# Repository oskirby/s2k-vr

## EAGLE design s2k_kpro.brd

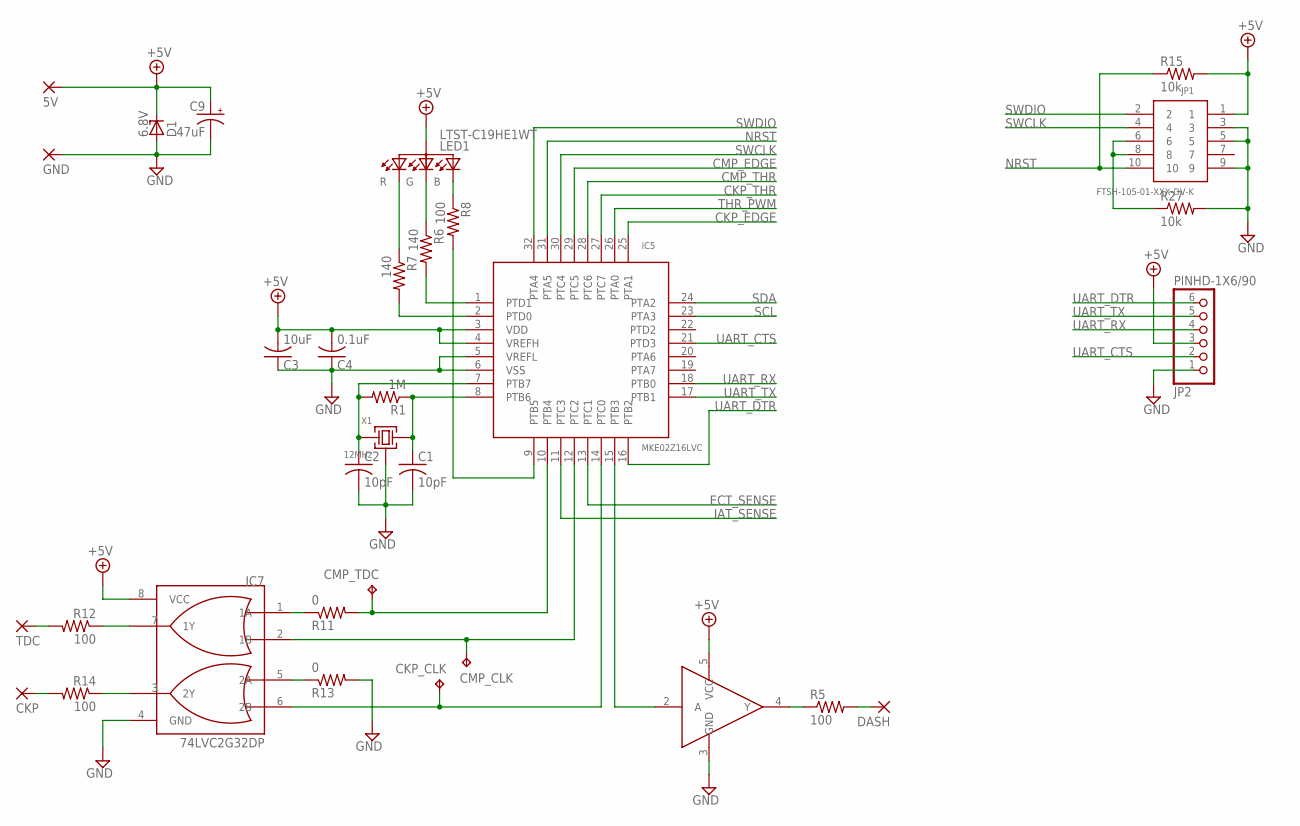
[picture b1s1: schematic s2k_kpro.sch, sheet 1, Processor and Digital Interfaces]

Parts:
5V: 5V; P1-20
C1, C2: 10pF; C0603
C3: 10uF; C0805
C4: 0.1uF; C0603
C9: 47uF; D/7343-31R
CKP: SIGPAD-P1-20; P1-20
CKP_CLK: TPB2,54; B2,54
CMP_CLK: TPB2,54; B2,54
CMP_TDC: TPB2,54; B2,54
D1: 6.8V; SOT23
DASH: SIGPAD-P1-20; P1-20
GND: SIGPAD-P1-20; P1-20
IC5: MKE02Z16LVC; LQFP32-7X7
IC6: 74LVC1G17SE; SOT353
IC7: 74LVC2G32DP; TSSOP8
JP1: FTSH-105-01-XXX-DV-K
JP2: PINHD-1X6/90; 1X06/90
LED1: LTST-C19HE1WT; LED-0606
R1: 1M; R0603
R5, R8, R12, R14: 100; R0603
R6, R7: 140; R0603
R11, R13: 0; R0603
R15, R27: 10k; R0603
TDC: SIGPAD-P1-20; P1-20
X1: 12MHz; SMD4-2520

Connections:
+5V: 5V.TP, C3.2, C4.2, C9.+, D1.3 (C), IC5.3 (VDD), IC5.4 (VREFH), IC6.5 (VCC), IC7.8 (VCC), JP1.1, JP2.3, LED1.4 (ANODE), R15.2; also elsewhere on the board
CAM_CLK: CMP_CLK.TP, IC5.12 (PTC2), IC7.2 (1B)
CAM_OUT: R12.2, TDC.TP
CAM_TDC: CMP_TDC.TP, IC5.10 (PTB4), R11.2
CKP_CLK: CKP_CLK.TP, IC5.14 (PTC0), IC7.6 (2B)
CKP_EDGE: IC5.25 (PTA1); also elsewhere on the board
CKP_THR: IC5.27 (PTC7); also elsewhere on the board
CMP_EDGE: IC5.29 (PTC5); also elsewhere on the board
CMP_THR: IC5.28 (PTC6); also elsewhere on the board
CRANK_OUT: CKP.TP, R14.2
ECT_OUT: DASH.TP, R5.2
ECT_PWM: IC5.15 (PTB3), IC6.2 (A)
ECT_SENSE: IC5.13 (PTC1); also elsewhere on the board
EXTAL: C2.1, IC5.7 (PTB7), R1.2, X1.3 (2)
GND: C1.2, C2.2, C3.1, C4.1, C9.-, D1.1 (A), GND.TP, IC5.5 (VREFL), IC5.6 (VSS), IC6.3 (GND), IC7.4 (GND), JP1.3, JP1.5, JP1.9, JP2.1, R13.2, R27.2, X1.2 (GND), X1.4 (GND); also elsewhere on the board
IAT_SENSE: IC5.11 (PTC3); also elsewhere on the board
LED_B: IC5.9 (PTB5), R8.2
LED_G: IC5.2 (PTD0), R7.2
LED_R: IC5.1 (PTD1), R6.2
unnamed: IC7.7 (1Y), R12.1
unnamed: IC7.1 (1A), R11.1
unnamed: LED1.2 (G), R6.1
unnamed: IC7.5 (2A), R13.1
unnamed: LED1.1 (R), R7.1
unnamed: LED1.3 (B), R8.1
unnamed: IC7.3 (2Y), R14.1
unnamed: IC6.4 (Y), R5.1
unnamed: JP1.6, JP1.8, R27.1
NRST: IC5.31 (PTA5), JP1.10, R15.1; also elsewhere on the board
SCL: IC5.23 (PTA3); also elsewhere on the board
SDA: IC5.24 (PTA2); also elsewhere on the board
SWCLK: IC5.30 (PTC4), JP1.4
SWDIO: IC5.32 (PTA4), JP1.2
THR_PWM: IC5.26 (PTA0); also elsewhere on the board
UART_CTS: IC5.21 (PTD3), JP2.2
UART_DTR: IC5.16 (PTB2), JP2.6
UART_RX: IC5.18 (PTB0), JP2.4
UART_TX: IC5.17 (PTB1), JP2.5
XTAL: C1.1, IC5.8 (PTB6), R1.1, X1.1

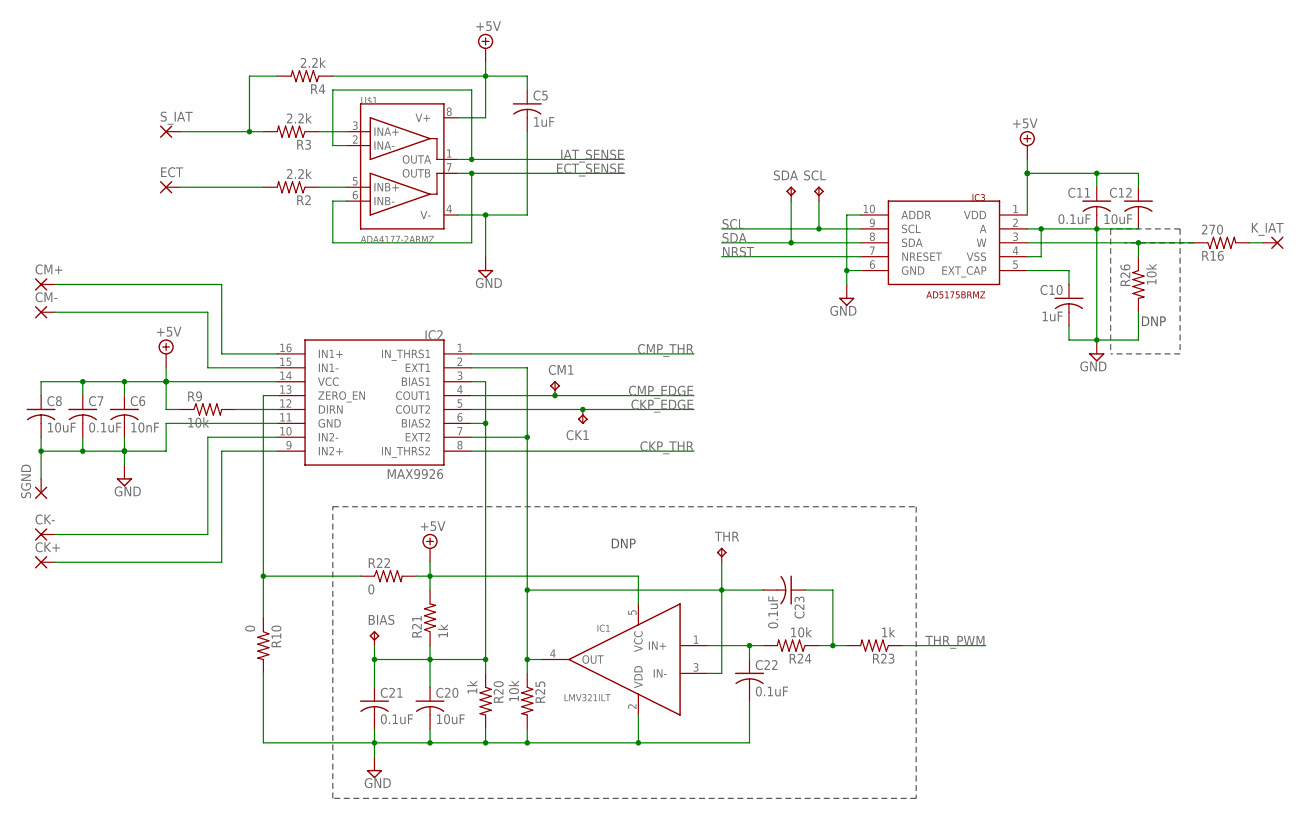
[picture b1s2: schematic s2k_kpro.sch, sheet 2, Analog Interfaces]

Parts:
BIAS: TPB2,54; B2,54
C5, C10: 1uF; C0603
C6: 10nF; C0306
C7, C11, C21, C22, C23: 0.1uF; C0603
C8, C12: 10uF; C0805
C20: 10uF; C0603
CK1: TPB2,54; B2,54
CK+: SIGPAD-P1-20; P1-20
CK-: SIGPAD-P1-20; P1-20
CM1: TPB2,54; B2,54
CM+: SIGPAD-P1-20; P1-20
CM-: SIGPAD-P1-20; P1-20
ECT: SIGPAD-P1-20; P1-20
IC1: LMV321ILT; SOT23-5L
IC2: MAX9926; 16-QSOP
IC3: AD5175BRMZ; MSOP10
K_IAT: SIGPAD-P1-20; P1-20
R2, R3, R4: 2.2k; R0603
R9, R24, R25, R26: 10k; R0603
R10, R22: 0; R0603
R16: 270; R0603
R20, R21, R23: 1k; R0603
SCL: TPB2,54; B2,54
SDA: TPB2,54; B2,54
SGND: SIGPAD-P1-20; P1-20
S_IAT: SIGPAD-P1-20; P1-20
THR: TPB2,54; B2,54
U$1: ADA4177-2ARMZ; MSOP08

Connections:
+5V: C5.1, C6.1, C7.1, C8.1, C11.1, C12.1, IC1.5 (VCC), IC2.14 (VCC), IC3.1 (VDD), R4.1, R9.1, R21.2, R22.2, U$1.8 (V+); also elsewhere on the board
CAM_IN+: CM+.TP, IC2.16 (IN1+)
CAM_IN-: CM-.TP, IC2.15 (IN1-)
CKP_EDGE: CK1.TP, IC2.5 (COUT2); also elsewhere on the board
CKP_THR: IC2.8 (IN_THRS2); also elsewhere on the board
CMP_EDGE: CM1.TP, IC2.4 (COUT1); also elsewhere on the board
CMP_THR: IC2.1 (IN_THRS1); also elsewhere on the board
CRANK_IN+: CK+.TP, IC2.9 (IN2+)
CRANK_IN-: CK-.TP, IC2.10 (IN2-)
ECT_SENSE: U$1.6 (INB-), U$1.7 (OUTB); also elsewhere on the board
GND: C5.2, C6.2, C7.2, C8.2, C10.2, C11.2, C12.2, C20.2, C21.2, C22.2, IC1.2 (VDD), IC2.11 (GND), IC3.2 (A), IC3.4 (VSS), IC3.6 (GND), IC3.10 (ADDR), R10.2, R20.2, R25.2, R26.2, SGND.TP, U$1.4 (V-); also elsewhere on the board
IAT_SENSE: U$1.1 (OUTA), U$1.2 (INA-); also elsewhere on the board
unnamed: R3.1, U$1.3 (INA+)
unnamed: R3.2, R4.2, S_IAT.TP
unnamed: R2.1, U$1.5 (INB+)
unnamed: IC2.12 (DIRN), R9.2
unnamed: ECT.TP, R2.2
unnamed: C22.1, IC1.1 (IN+), R24.2
unnamed: IC2.13 (ZERO_EN), R10.1, R22.1
unnamed: C23.1, R23.2, R24.1
unnamed: C23.2, IC1.3 (IN-), IC1.4 (OUT), IC2.2 (EXT1), IC2.7 (EXT2), R25.1, THR.TP
unnamed: C10.1, IC3.5 (EXT_CAP)
unnamed: IC3.3 (W), R16.1, R26.1
unnamed: K_IAT.TP, R16.2
NRST: IC3.7 (NRESET); also elsewhere on the board
SCL: IC3.9 (SCL), SCL.TP; also elsewhere on the board
SDA: IC3.8 (SDA), SDA.TP; also elsewhere on the board
THR_PWM: R23.1; also elsewhere on the board
VR_BIAS: BIAS.TP, C20.1, C21.1, IC2.3 (BIAS1), IC2.6 (BIAS2), R20.1, R21.1

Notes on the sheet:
DNP

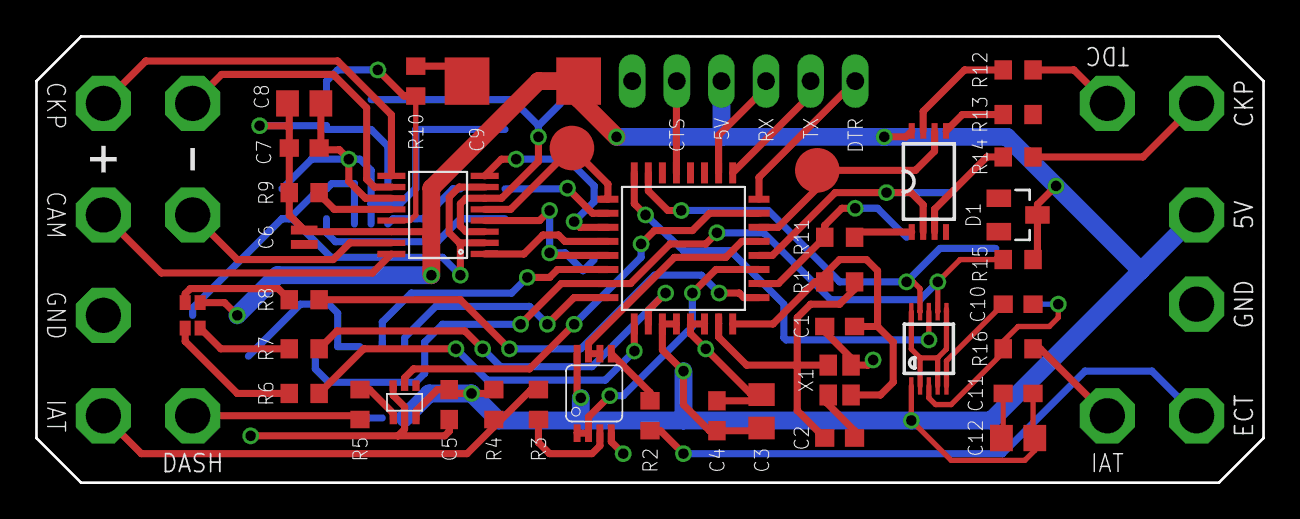
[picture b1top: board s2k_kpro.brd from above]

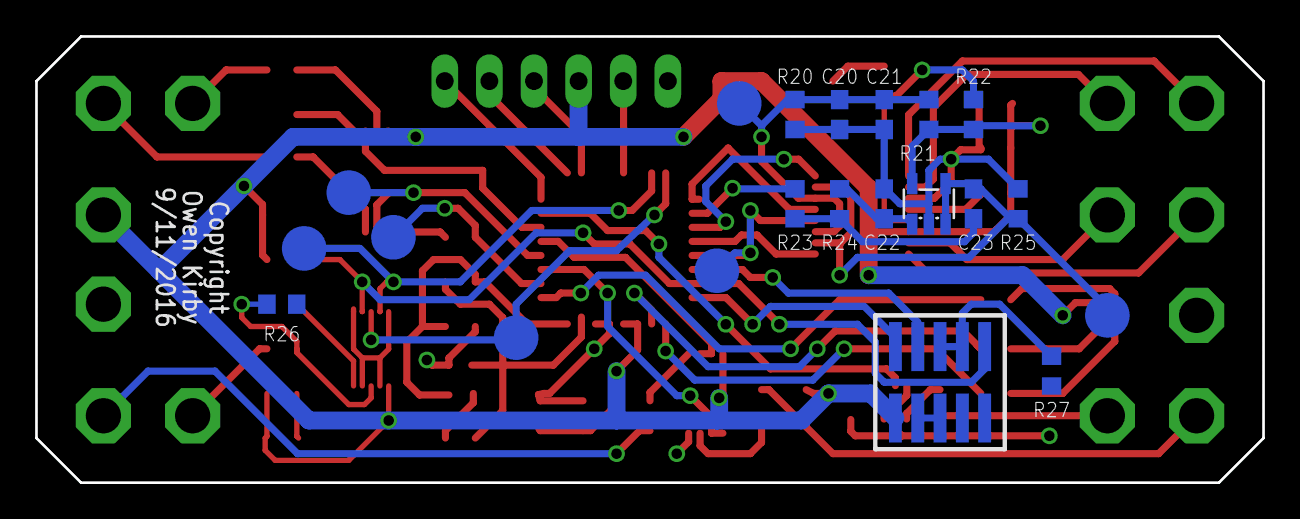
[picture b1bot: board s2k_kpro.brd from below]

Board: 2 copper layers, 69.8 x 25.4 mm, 74 parts (22 on the bottom side), 56 nets.

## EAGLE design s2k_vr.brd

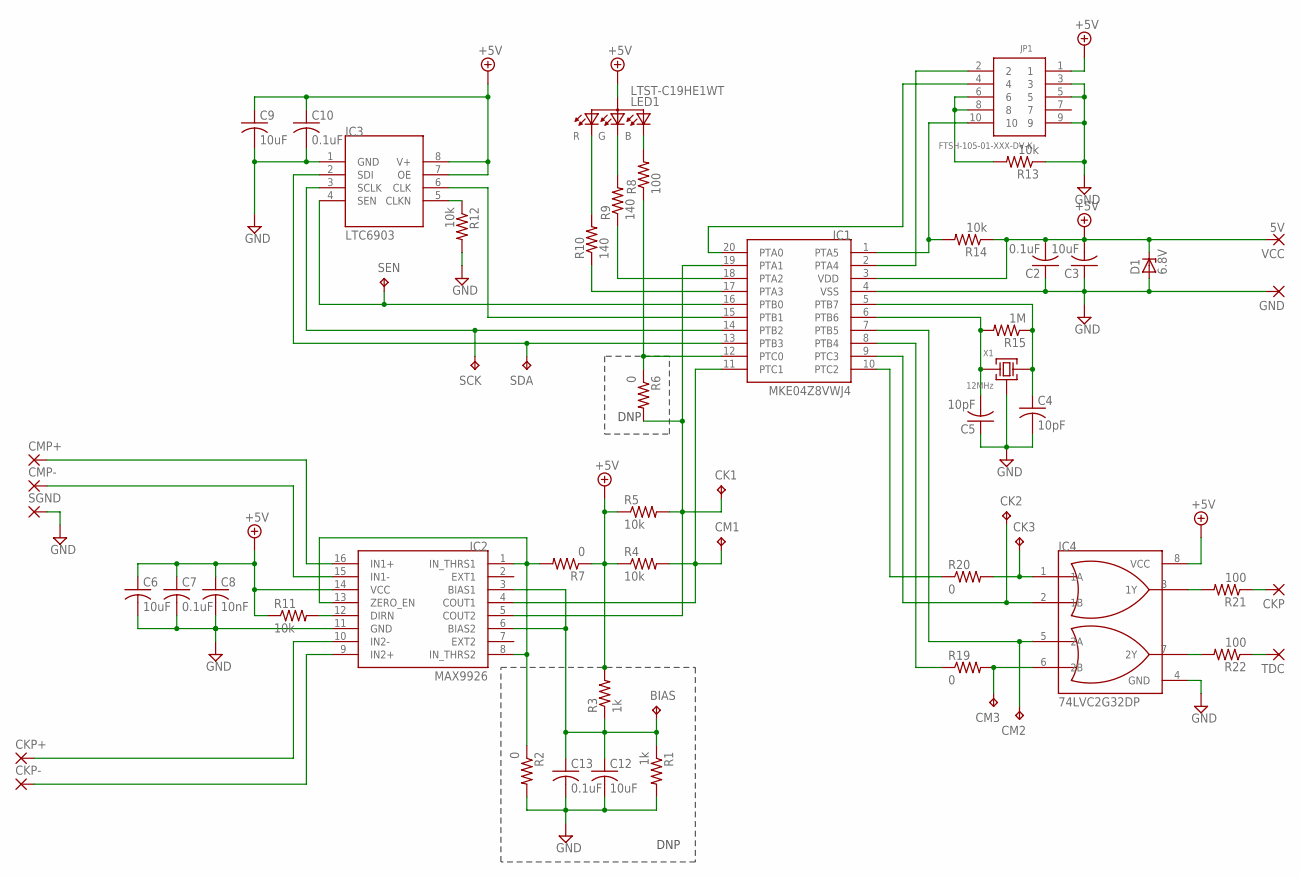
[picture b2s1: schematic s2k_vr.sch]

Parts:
BIAS: TPB2,54; B2,54
C2, C7, C10, C13: 0.1uF; C0603
C3, C6, C9: 10uF; C0805
C4, C5: 10pF; C0603
C8: 10nF; C0306
C12: 10uF; C0603
CK1, CK2, CK3: TPB2,54; B2,54
CKP: 3,81/1,4
CKP+: 3,81/1,4
CKP-: 3,81/1,4
CM1, CM2, CM3: TPB2,54; B2,54
CMP+: 3,81/1,4
CMP-: 3,81/1,4
D1: 6.8V; SOT23
GND: 3,81/1,4
IC1: MKE04Z8VWJ4; SOIC20S
IC2: MAX9926; 16-QSOP
IC3: LTC6903; MS8
IC4: 74LVC2G32DP; TSSOP8
JP1: FTSH-105-01-XXX-DV-K
LED1: LTST-C19HE1WT; LED-0606
R1, R3: 1k; R0603
R2, R6, R7, R19, R20: 0; R0603
R4, R5, R11, R12, R13, R14: 10k; R0603
R8, R21, R22: 100; R0603
R9, R10: 140; R0603
R15: 1M; R0603
SCK: TPB2,54; B2,54
SDA: TPB2,54; B2,54
SEN: TPB2,54; B2,54
SGND: 3,81/1,4
TDC: 3,81/1,4
VCC: 5V; 3,81/1,4
X1: 12MHz; SMD4-2520

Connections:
+5V: C2.2, C3.2, C6.1, C7.1, C8.1, C9.1, C10.1, D1.3 (C), IC1.3 (VDD), IC2.14 (VCC), IC3.7 (OE), IC3.8 (V+), IC4.8 (VCC), JP1.1, LED1.4 (ANODE), R3.2, R4.1, R5.1, R7.1, R11.1, R14.1, VCC.1
CAM_EDGE: CM1.TP, IC1.11 (PTC1), IC2.4 (COUT1), R4.2
CAM_IN+: CKP+.1, IC2.10 (IN2-)
CAM_IN-: CKP-.1, IC2.9 (IN2+)
CAM_OUT: R22.1, TDC.1
CAM_PULSE: CK2.TP, IC1.9 (PTC3), IC4.2 (1B)
CAM_TDC: CK3.TP, IC4.1 (1A), R20.2
CLK: IC1.15 (PTB1), IC3.6 (CLK)
CRANK_EDGE: CK1.TP, IC1.19 (PTA1), IC2.5 (COUT2), R5.2, R6.2
CRANK_IN+: CMP+.1, IC2.16 (IN1+)
CRANK_IN-: CMP-.1, IC2.15 (IN1-)
CRANK_OUT: CKP.1, R21.1
CRANK_PULSE: CM2.TP, IC1.7 (PTB5), IC4.5 (2A)
GND: C2.1, C3.1, C4.2, C5.1, C6.2, C7.2, C8.2, C9.2, C10.2, C12.2, C13.2, D1.1 (A), GND.1, IC1.4 (VSS), IC2.11 (GND), IC3.1 (GND), IC4.4 (GND), JP1.3, JP1.5, JP1.9, R1.2, R2.2, R12.2, R13.1, SGND.1, X1.2 (GND), X1.4 (GND)
MOSI: IC1.13 (PTB3), IC3.2 (SDI), SDA.TP
unnamed: IC2.12 (DIRN), R11.2
unnamed: IC1.18 (PTA2), R9.1
unnamed: LED1.3 (B), R8.2
unnamed: C4.1, IC1.5 (PTB7), R15.1, X1.1
unnamed: IC1.17 (PTA3), R10.1
unnamed: IC3.5 (CLKN), R12.1
unnamed: IC1.12 (PTC0), R6.1, R8.1
unnamed: IC1.8 (PTB4), R19.1
unnamed: IC1.10 (PTC2), R20.1
unnamed: BIAS.TP, C12.1, C13.1, IC2.3 (BIAS1), IC2.6 (BIAS2), R1.1, R3.1
unnamed: LED1.2 (G), R9.2
unnamed: IC4.3 (1Y), R21.2
unnamed: LED1.1 (R), R10.2
unnamed: JP1.6, JP1.8, R13.2
unnamed: CM3.TP, IC4.6 (2B), R19.2
unnamed: C5.2, IC1.6 (PTB6), R15.2, X1.3 (2)
unnamed: IC2.1 (IN_THRS1), IC2.8 (IN_THRS2), IC2.13 (ZERO_EN), R2.1, R7.2
unnamed: IC4.7 (2Y), R22.2
NRST: IC1.1 (PTA5), JP1.10, R14.2
SPICK: IC1.14 (PTB2), IC3.3 (SCLK), SCK.TP
SPIEN: IC1.16 (PTB0), IC3.4 (SEN), SEN.TP
SWCLK: IC1.20 (PTA0), JP1.4
SWDIO: IC1.2 (PTA4), JP1.2

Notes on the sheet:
DNP

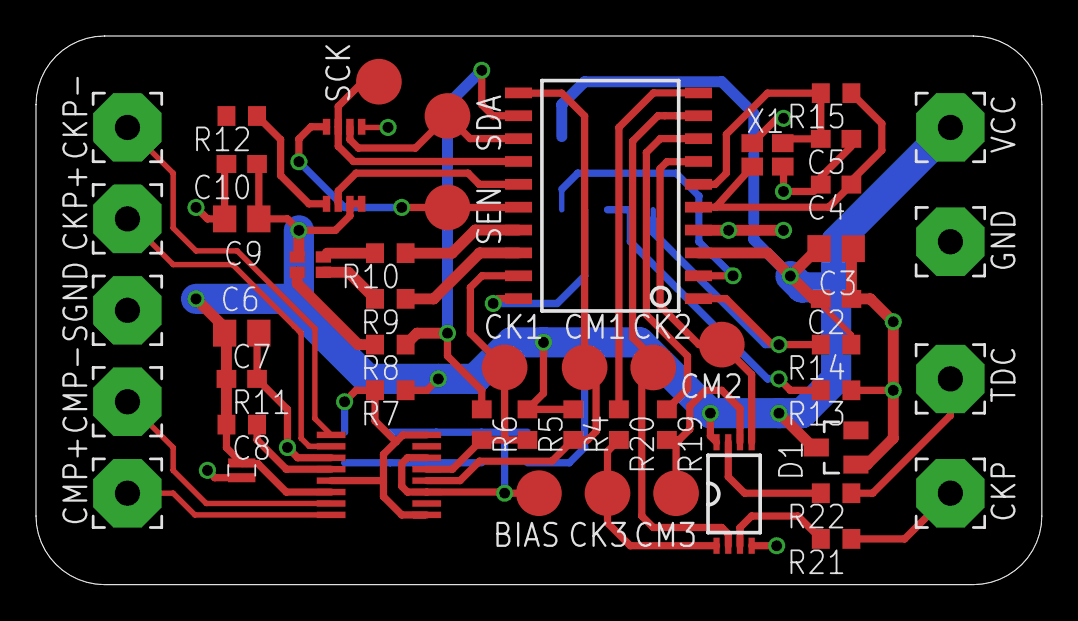
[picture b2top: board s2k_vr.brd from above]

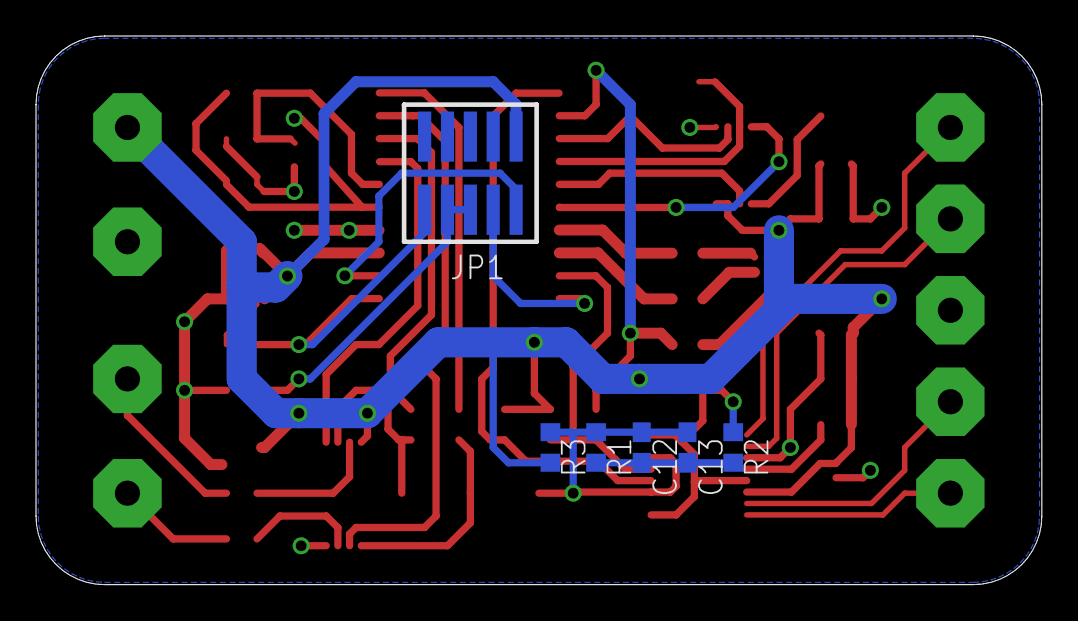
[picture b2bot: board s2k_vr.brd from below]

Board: 2 copper layers, 55.9 x 30.5 mm, 57 parts (6 on the bottom side), 38 nets.

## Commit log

2016-08-31 Initial commit of parts.lbr
2016-09-01 Initial commit of VR board schematic
2016-09-02 Add test pads and JTAG header
2016-09-03 Switch to MAX9926 and add output resistors
2016-09-03 Use Lite-On RGB LED
2016-09-05 Completed board layout
2016-09-06 Replace crystal with CX2520DB and reshuffle timer output channels.
2016-09-12 Redesign to handle IAT and ECT sensors
    Add analog interfaces to interpret the intake air temperature and engine coolant temperature. The IAT drives a programmable resistor for simulating an K-series IAT sensor and the ECT drives a PWM out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
2016-09-12 Final review, sent for manufacturing.
2016-09-13 Add BOM for S2000/K-Pro board
